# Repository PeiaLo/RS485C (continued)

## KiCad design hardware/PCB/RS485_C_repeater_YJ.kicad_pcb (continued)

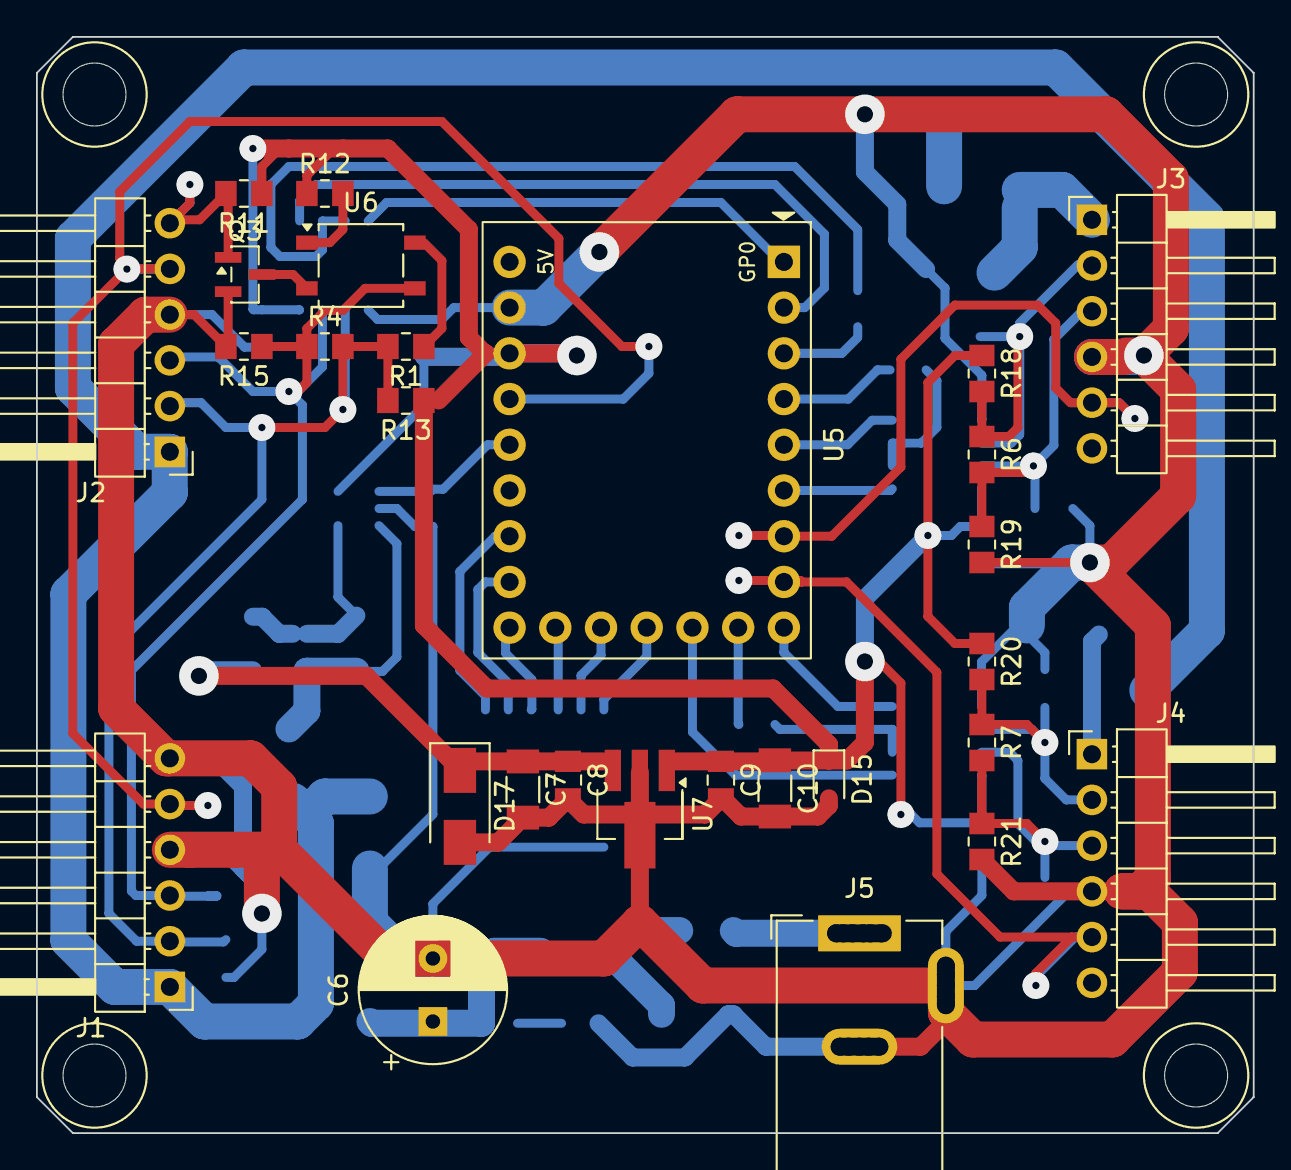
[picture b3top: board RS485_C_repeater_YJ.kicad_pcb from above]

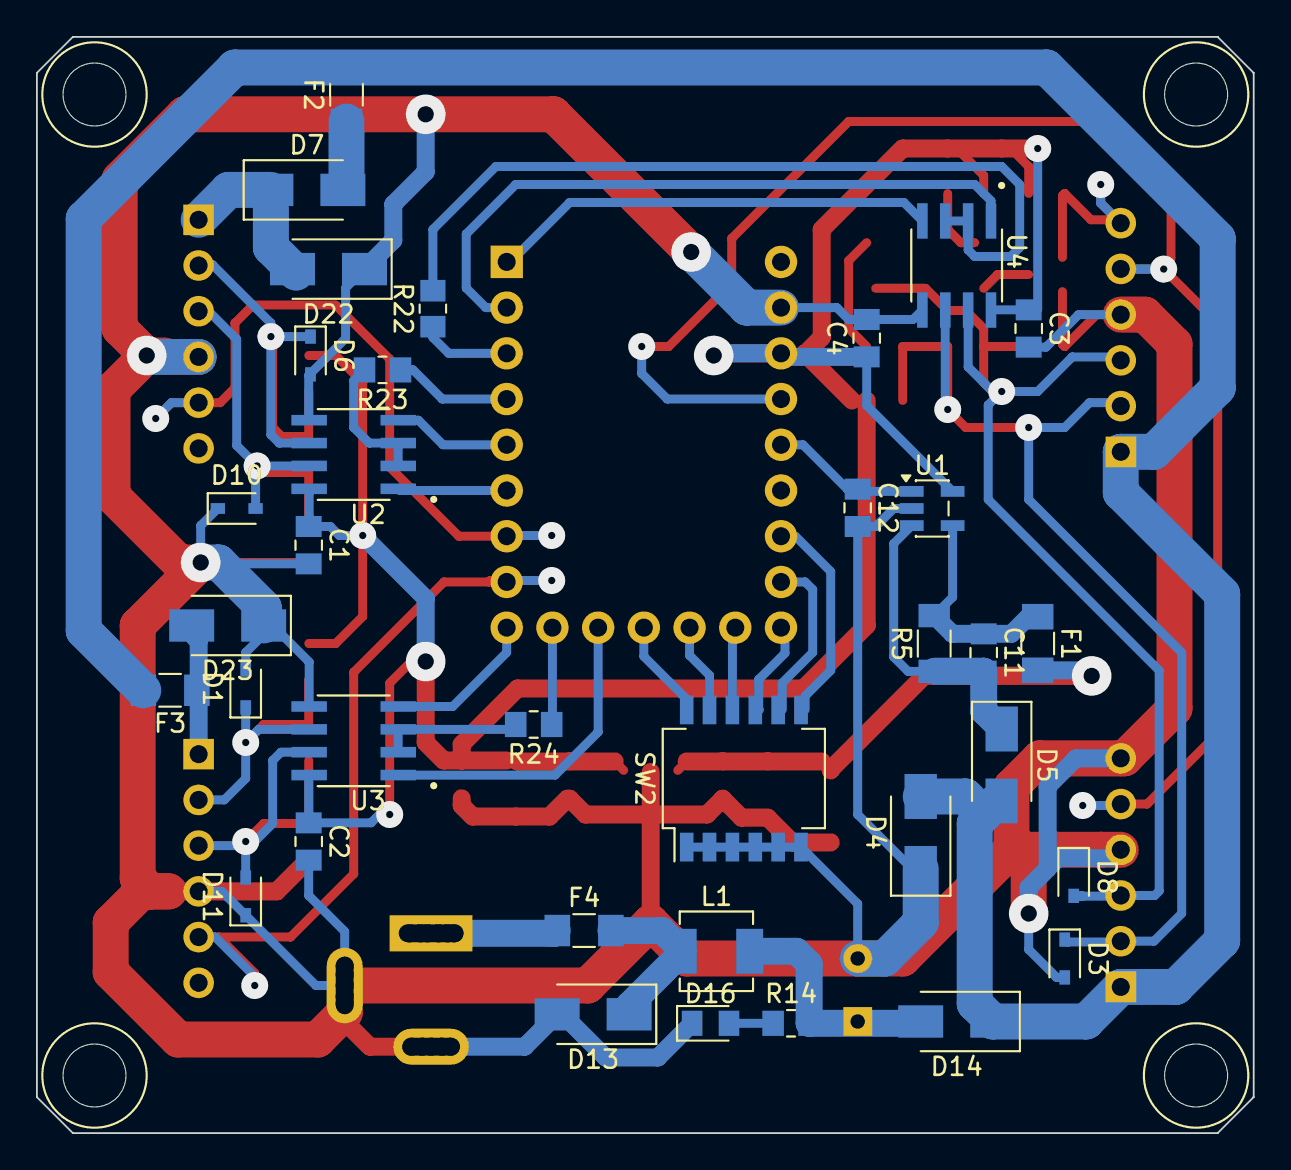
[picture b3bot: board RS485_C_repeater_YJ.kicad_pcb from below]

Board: 2 copper layers, 67.6 x 60.9 mm, 64 parts (35 on the bottom side), 45 nets.

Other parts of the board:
BRD1: Outline_M3; RS485_C_repeater_YJ_Outline_M3
